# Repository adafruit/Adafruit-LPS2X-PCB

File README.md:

## Adafruit LPS2X family of absolute pressure sensors PCB

<a href="http://www.adafruit.com/products/4530"><br/>
<a href="http://www.adafruit.com/products/4633"><br/>
Click here to purchase one from the Adafruit shop</a>

PCB files for the Adafruit LPS2X family of absolute pressure sensors. 

Format is EagleCAD schematic and board layout
* https://www.adafruit.com/product/4530
* http://www.adafruit.com/products/4633

### Description

We live on a planet with an atmosphere, a big ocean of gaseous air that keeps everything alive - and that atmosphere is constantly bouncing off of us, exerting air pressure on everything around us. But, how much air is in the atmosphere, bearing down on us?
Absolute pressure sensors  like the **ST LPS22HB** or **ST LPS25HB** can quickly and easily measure this air pressure, useful when you want to know about the weather (are we in a low pressure or high pressure system?) or to determine altitude, as the air thins out the higher we get above sea level. For example, at sea level, the official pressure level is **1013.25 hPa**. You can use these sensors to measure the current pressure where you are right now, to compare.

The LPS25 has a wide measurement range of **260-1260** hPa with 24-bit pressure data measurements that can be read up to  25 times a second (Hz), you can be confident that you always have an up to date and precise measurement. The LPS22 has the same measurement range but offers additional measurement rates of 50 and 75Hz. They’re pretty dang accurate too, with the ability to measure within 0.2 hPa after calibration (± 1 hPa before calibration).
### License

Adafruit invests time and resources providing this open source design, please support Adafruit and open-source hardware by purchasing products from [Adafruit](https://www.adafruit.com)!

Designed by Limor Fried/Ladyada for Adafruit Industries.

Creative Commons Attribution/Share-Alike, all text above must be included in any redistribution. 
See license.txt for additional details.

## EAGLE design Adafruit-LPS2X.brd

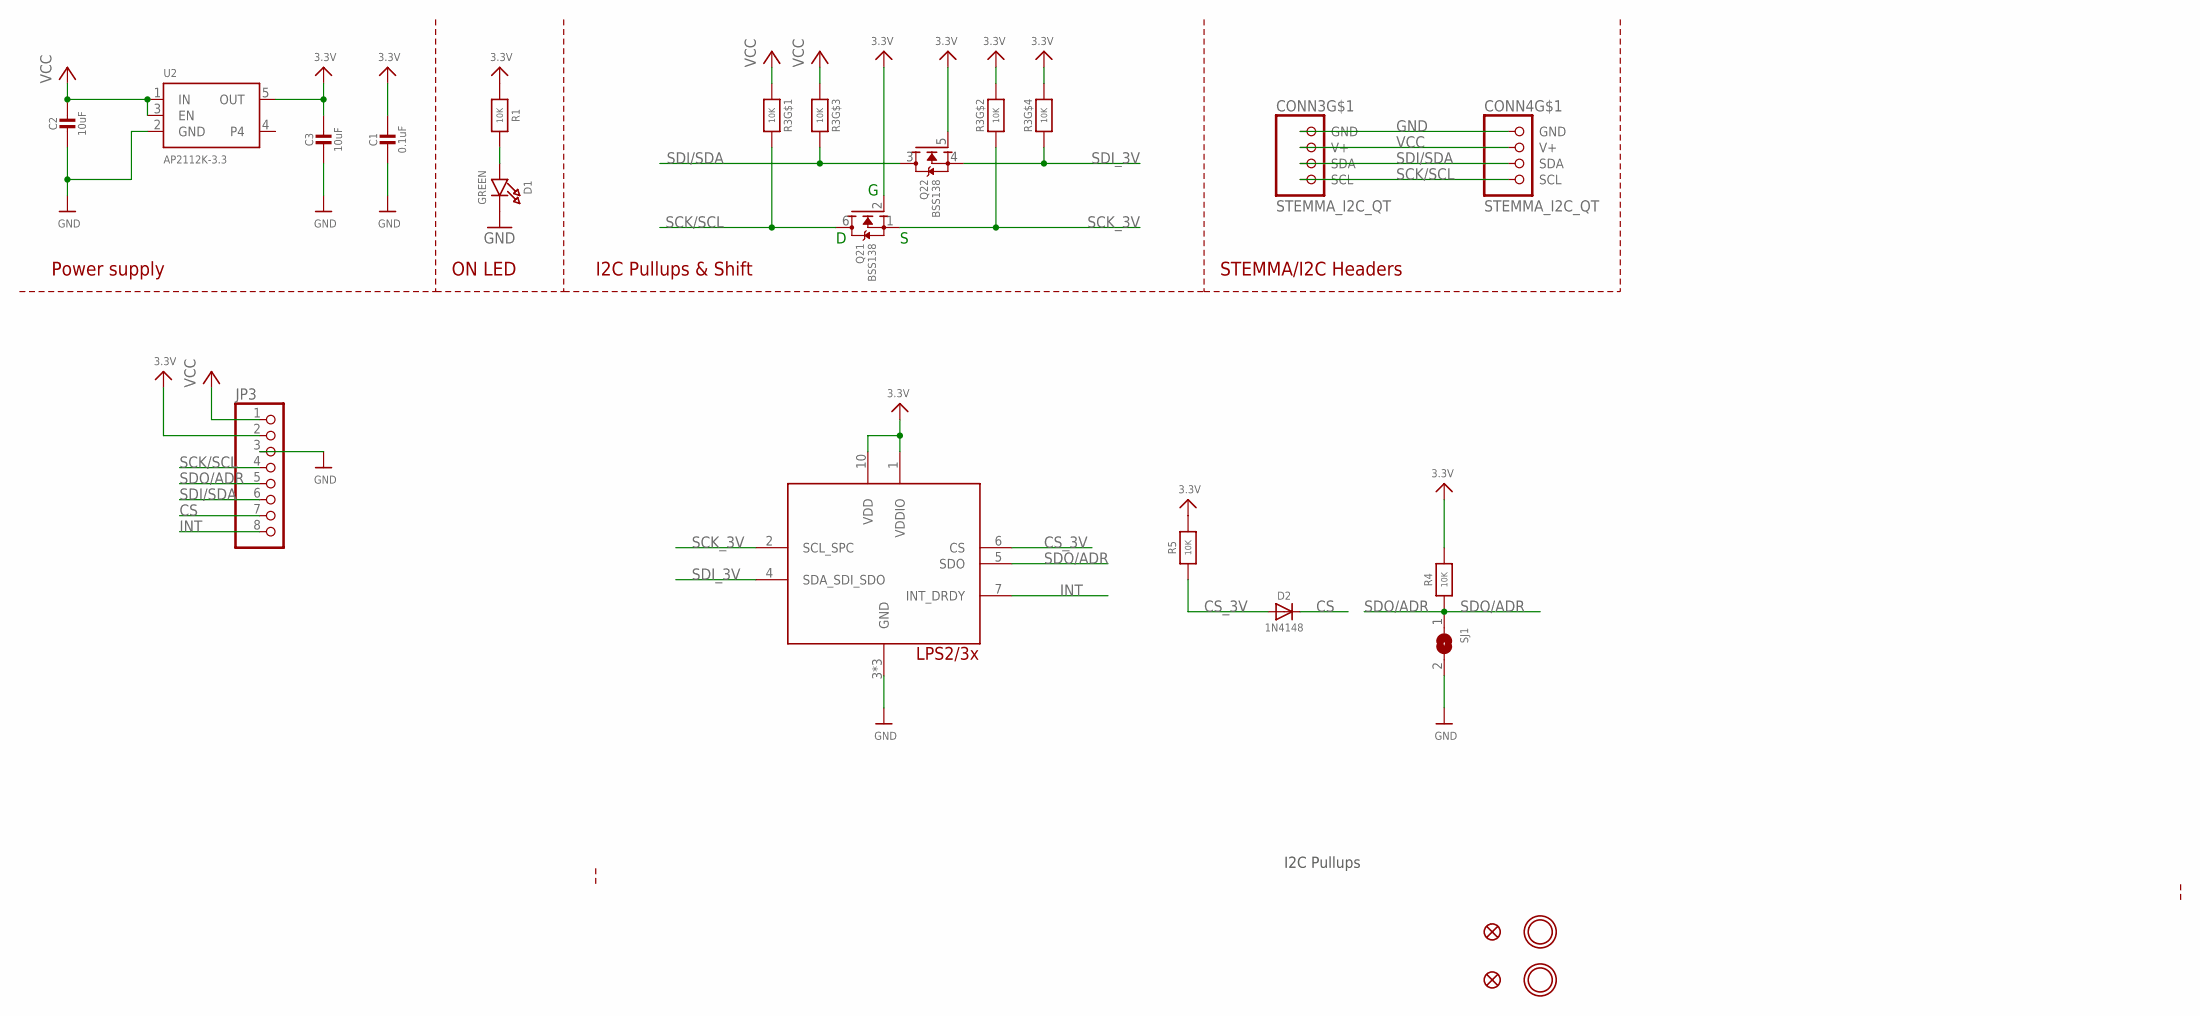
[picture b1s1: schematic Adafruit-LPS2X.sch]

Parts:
C1: 0.1uF; 0603-NO
C2, C3: 10uF; 0805-NO
CONN3, CONN4: STEMMA_I2C_QT; JST_SH4
D1: GREEN; CHIPLED_0603_NOOUTLINE
D2: 1N4148; SOD-323
FID3, FID4: FIDUCIAL_1MM
JP3: HEADER-1X8ROUND; 1X08_ROUND
Q2: BSS138; SOT363
R1, R4, R5: 10K; 0603-NO
R3: 10K; RESPACK_4X0603
SJ1: SOLDERJUMPER; SOLDERJUMPER_ARROW_NOPASTE
U2: AP2112K-3.3; SOT23-5
U$1, U$17: MOUNTINGHOLE2.5; MOUNTINGHOLE_2.5_PLATED
U$2: LPS2XHLGA; HLGA-10L

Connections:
3.3V: C1.1, C3.1, JP3.2, Q2.2 (G), Q2.5 (G), R1.1, R3.2 (1), R3.4 (1), R4.2, R5.2, U2.5 (OUT), U$2.1 (VDDIO), U$2.10 (VDD)
CS: D2.C, JP3.7
CS_3V: D2.A, R5.1, U$2.6 (CS)
GND: C1.2, C2.2, C3.2, CONN3.1 (GND), CONN4.1 (GND), D1.C, JP3.3, SJ1.2, U2.2 (GND), U$2.3 (GND), U$2.8 (GND), U$2.9 (GND)
INT: JP3.8, U$2.7 (INT_DRDY)
unnamed: D1.A, R1.2
SCK/SCL: CONN3.4 (SCL), CONN4.4 (SCL), JP3.4, Q2.6 (D), R3.8 (2)
SCK_3V: Q2.1 (S), R3.7 (2), U$2.2 (SCL_SPC)
SDI/SDA: CONN3.3 (SDA), CONN4.3 (SDA), JP3.6, Q2.3 (D), R3.6 (2)
SDI_3V: Q2.4 (S), R3.5 (2), U$2.4 (SDA_SDI_SDO)
SDO/ADR: JP3.5, R4.1, SJ1.1, U$2.5 (SDO)
VCC: C2.1, CONN3.2 (V+), CONN4.2 (V+), JP3.1, R3.1, R3.3 (1), U2.1 (IN), U2.3 (EN)

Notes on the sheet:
I2C Pullups & Shift
STEMMA/I2C Headers
ON LED
Power supply
I2C Pullups

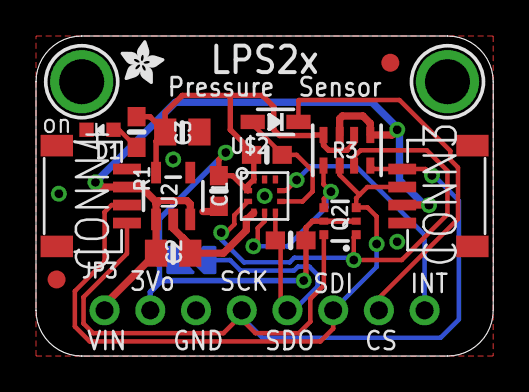
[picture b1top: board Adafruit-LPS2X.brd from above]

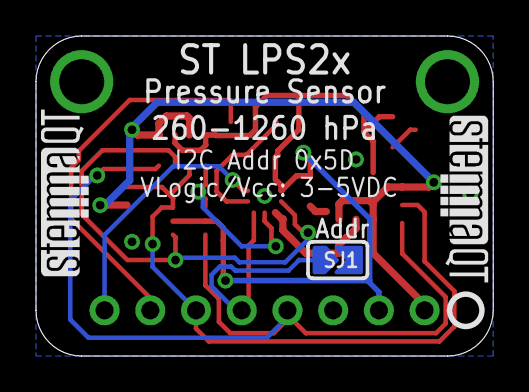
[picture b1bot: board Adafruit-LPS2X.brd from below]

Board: 2 copper layers, 25.4 x 17.8 mm, 24 parts (4 on the bottom side), 12 nets.

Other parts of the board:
U$4: ADAFRUIT_2.5MM
U$25: PCBFEAT-REV-040
U$30, U$31: STEMMAQT

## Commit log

2020-02-24 initial comit
2020-06-10 adding LPS22

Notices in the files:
parts and their libraries:
microbuilder: This work is placed in the public domain, and may be freely used for commercial and non-commercial work with the following conditions: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
